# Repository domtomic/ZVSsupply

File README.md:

# ZVSsupply
ZVS high voltage supply schematic and PCB layout project

Jumper needed to connect two Drain electrodes
All circuit is on back copper

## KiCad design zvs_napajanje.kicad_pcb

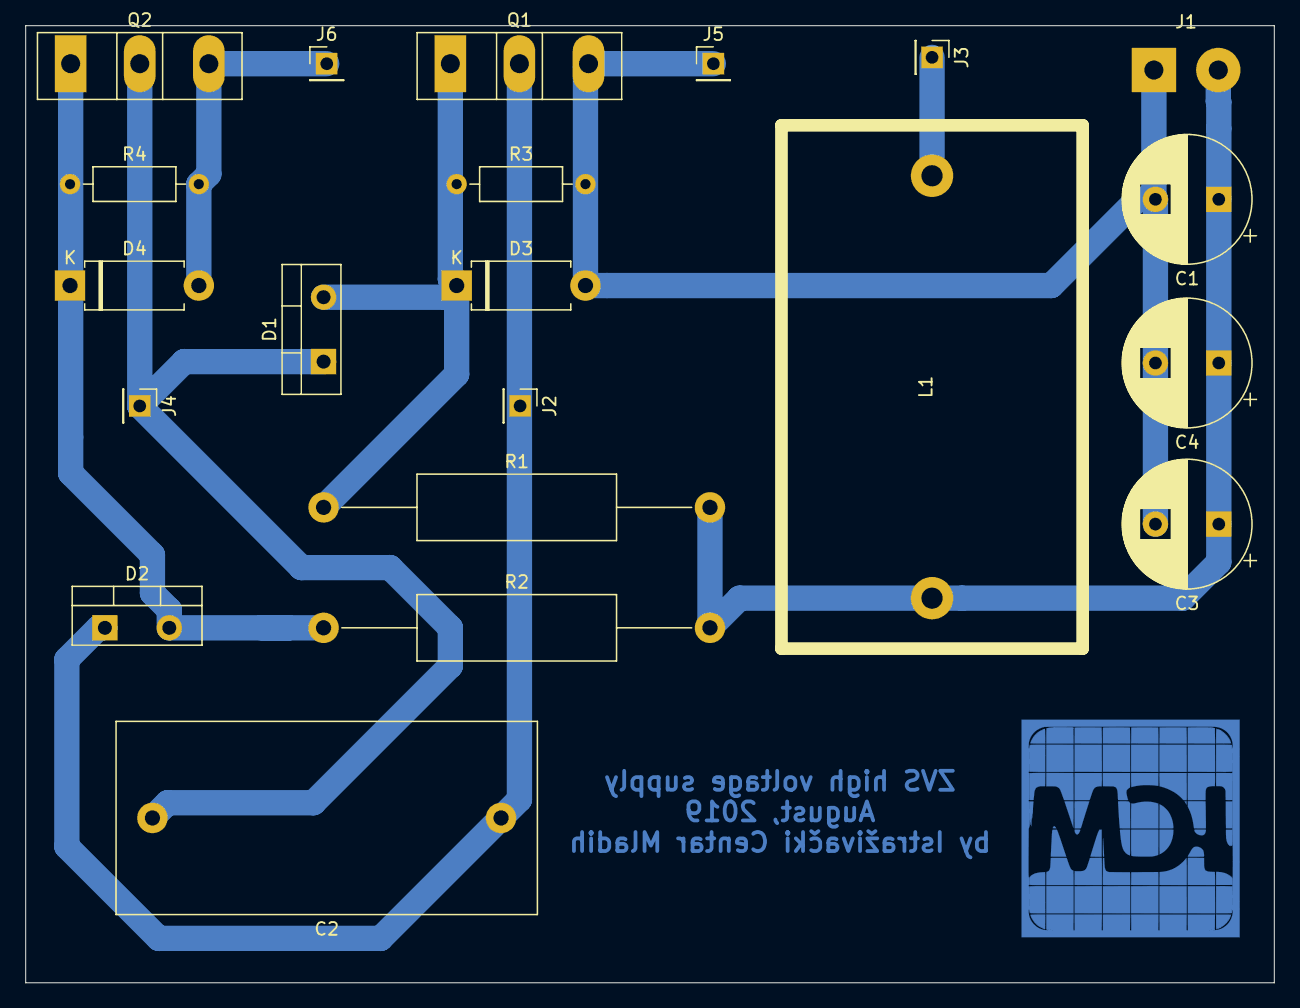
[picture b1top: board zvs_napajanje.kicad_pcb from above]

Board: 2 copper layers, 98.5 x 75.5 mm, 21 parts (0 on the bottom side), 8 nets.

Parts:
C1, C3, C4: 470u; CP_Radial_D10.0mm_P5.00mm
C2: 0.68u; C_Rect_L33.0mm_W15.0mm_P27.50mm_MKS4
D1, D2: MUR1560G; TO-220-2_Vertical
D3, D4: 1N5349-12V; D_DO-15_P10.16mm_Horizontal
J1: ulaz; SolderWirePad_1x02_P5.08mm_Drill1.5mm
J2, J3, J4: Conn_01x01_Female; PinHeader_1x01_P2.54mm_Vertical
J5, J6: VEE_JUMPER; PinHeader_1x01_P2.54mm_Vertical
L1: 100u; zvsojnica
Q1, Q2: IRFP250; TO-247-3_Vertical
R1, R2: 470; R_Axial_DIN0516_L15.5mm_D5.0mm_P30.48mm_Horizontal
R3, R4: 10k; R_Axial_DIN0207_L6.3mm_D2.5mm_P10.16mm_Horizontal

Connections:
unnamed: C2.1, D2.1, J2.1, Q1.2
unnamed: C2.2, D1.1, J4.1, Q2.2
unnamed: D1.2, D3.1, Q1.1, R1.1, R3.1
unnamed: D2.2, D4.1, Q2.1, R2.1, R4.1
unnamed: D4.2, J6.1, Q2.3, R4.2
unnamed: J3.1, L1.2
VDD: C1.1, C3.1, C4.1, J1.2, L1.1, R1.2, R2.2
VEE: C1.2, C3.2, C4.2, D3.2, J1.1, J5.1, Q1.3, R3.2

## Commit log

2019-08-03 First commit: finished schematic with footprints, started layout
2019-08-03 added L1 footprint
2019-08-03 changed gitignore to include netlist and BOM
2019-08-09 Added heatsink, fixed footprints; Experimental layout
2019-08-09 updated netlist file
2019-08-09 added heatsink design parameters
2019-08-09 almost over
2019-08-09 almost almost over
2019-08-09 finished layout
